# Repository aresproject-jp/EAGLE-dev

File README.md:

# EAGLE-dev
## projects
ARES3号機向けの回路の共同開発用ワークスペースです。
EAGLEのschファイルとbrdファイルを同じ名前のフォルダ内に保存して管理して下さい。
EAGLEの推奨バージョンは9.6.2です。
## libraries
各モジュールのライブラリを共有します。/computers /sensors /element /motor /connectorの5つの
フォルダを用意しています。以下の基準に従って分類して下さい。
- computers : コンピュータ及びマイクロコンピュータ　ex)jetson nano, raspberypi, arduino
- sensors   : 各センサモジュール　ex)BNO055, BMP180
- element   : 回路素子　ex)PchMosfet, DCDCconverter
- motor     : モーター関連のモジュール　ex)モータードライバ, エンコーダ
- connector : コネクタ類
## 3Dmodels
EAGLEにデフォルトで3Dデータが登録されていない部品の3Dデータ(*step)をアップロードしてください。
分類方法はlibrariesと同様です。
## documets
参考資料およびシステム図

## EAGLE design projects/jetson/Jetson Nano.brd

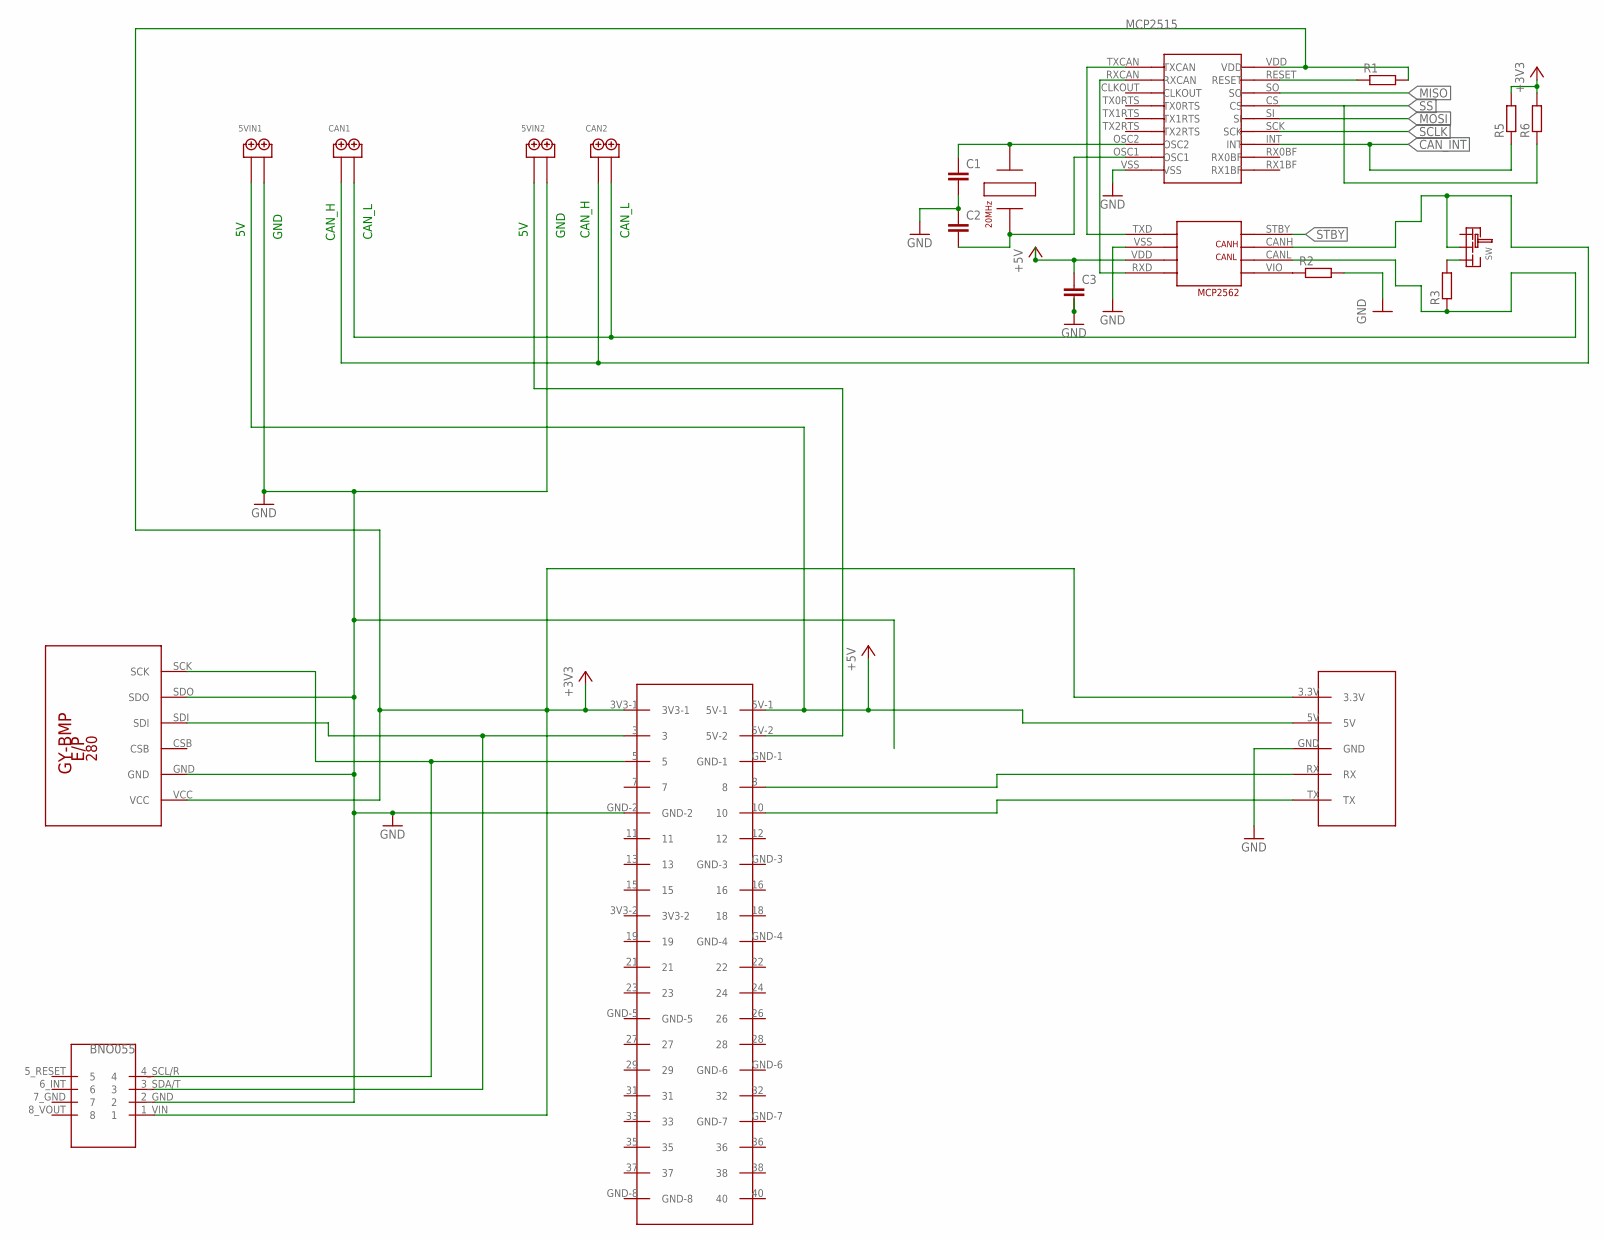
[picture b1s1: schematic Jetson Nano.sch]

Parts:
5VIN1, 5VIN2: 2PIN
C1, C2, C3: C-EU025-024X044; C025-024X044
CAN1, CAN2: 2PIN
JN1: JETSON_NANO
MCP1: MCP2515
R1, R2, R3, R5, R6: R-EU_0207/10; 0207/10
SW: SRIDE_SWITCH
U$1: GY-BPM280; GY-BMP280-FOOTPRINT
U$2: BNO055
U$3: WIRELESS_PINS
U$4: MCP2562
U$5: HUSG20

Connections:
5V_2: 5VIN2.P$1, JN1.5V-2
+3V3: JN1.3V3-1, MCP1.VDD, R1.2, R5.2, R6.2, U$1.VCC, U$2.1_VIN (1), U$3.3.3V
+5V_1: 5VIN1.P$1, C3.1, JN1.5V-1, U$3.5V, U$4.VDD
CAN_H2: CAN1.P$1, CAN2.P$1, SW.LR, U$4.CANH
CAN_INT: MCP1.INT, R5.1
GND: 5VIN1.P$2, 5VIN2.P$2, C1.2, C2.1, C3.2, JN1.GND-2, MCP1.VSS, U$1.GND, U$1.SDO, U$2.2_GND (2), U$3.GND, U$4.VSS
MISO: MCP1.SO
MOSI: MCP1.SI
unnamed: JN1.3, U$1.SDI, U$2.3_SDA/T (3)
unnamed: JN1.5, U$1.SCK, U$2.4_SCL/R (4)
unnamed: C1.1, MCP1.OSC2, U$5.A
unnamed: C2.2, MCP1.OSC1, U$5.B
unnamed: MCP1.TXCAN, U$4.TXD
unnamed: MCP1.RXCAN, U$4.RXD
unnamed: JN1.8, U$3.RX
unnamed: JN1.10, U$3.TX
unnamed: MCP1.RESET, R1.1
unnamed: R2.1, U$4.VIO
unnamed: R3.2, SW.R
unnamed: CAN1.P$2, CAN2.P$2, R3.1, U$4.CANL
SCLK: MCP1.SCK
SS: MCP1.CS, R6.1
STBY: U$4.STBY

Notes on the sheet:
GND
CAN_H
CAN_L

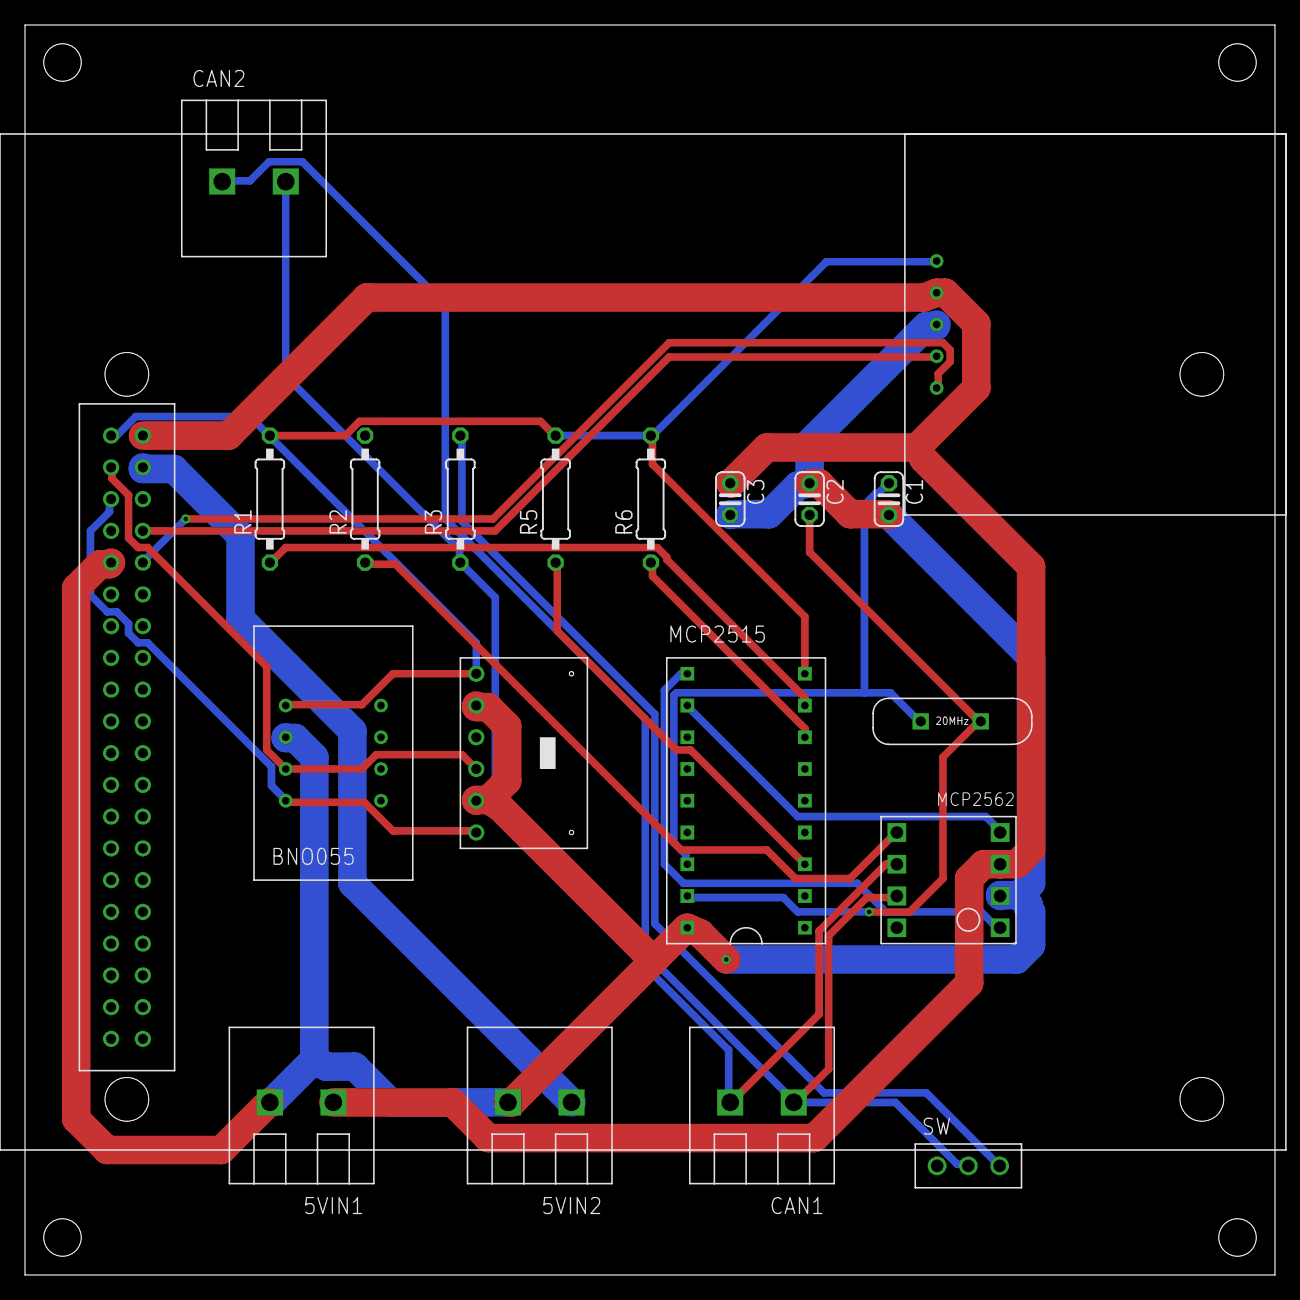
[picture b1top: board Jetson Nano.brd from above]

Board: 2 copper layers, 100.0 x 100.0 mm, 20 parts (0 on the bottom side), 19 nets.

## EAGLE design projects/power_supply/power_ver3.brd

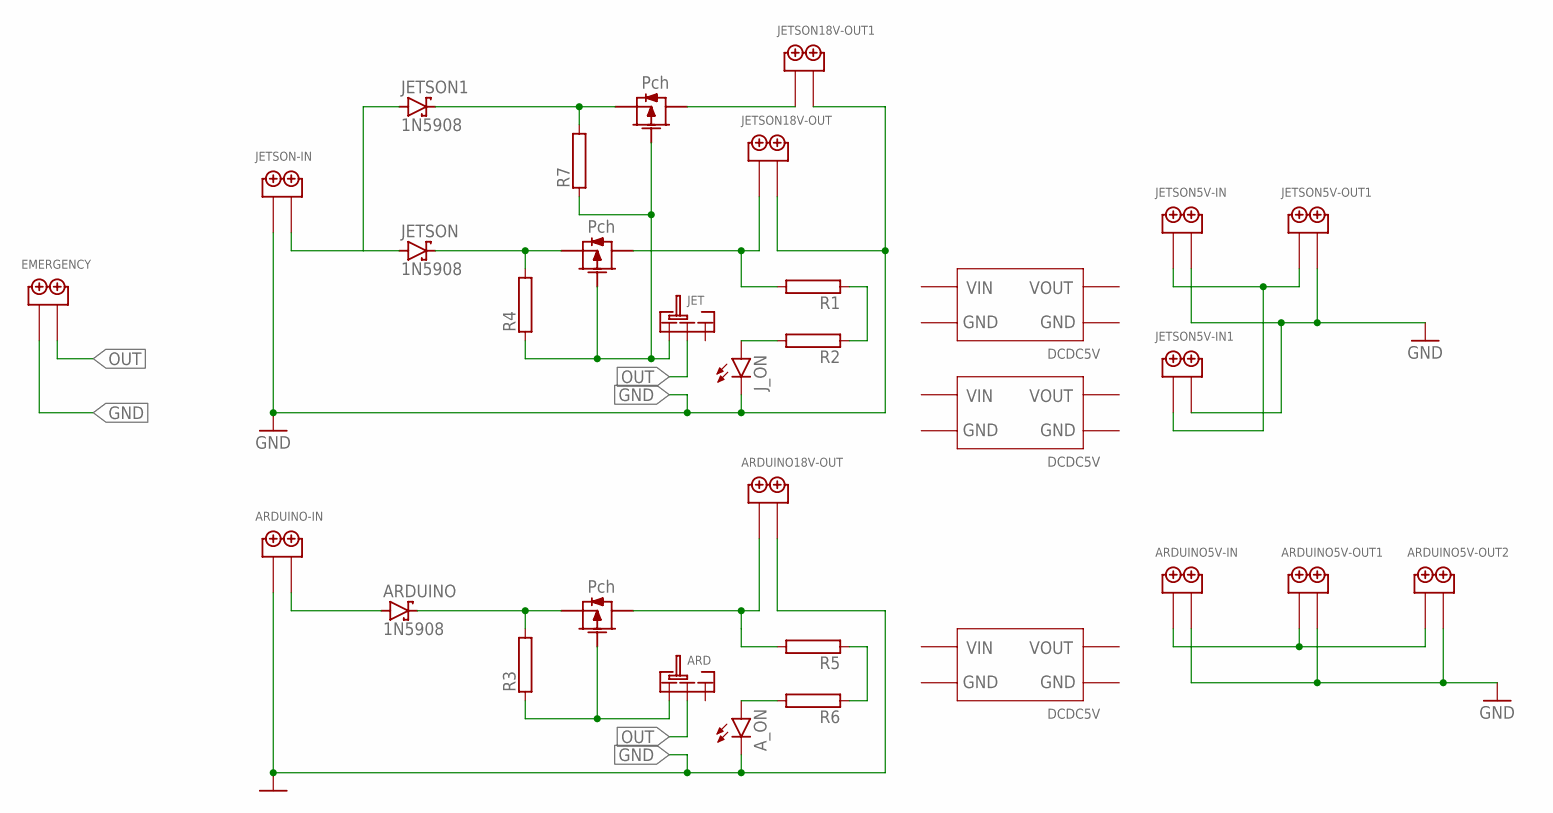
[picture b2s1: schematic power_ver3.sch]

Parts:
ARD: SRIDE_SWITCH
ARDUINO: 1N5908; C4111-15
ARDUINO5V-IN, ARDUINO5V-OUT1, ARDUINO5V-OUT2, ARDUINO18V-OUT: 2PIN
ARDUINO-IN: 2PIN
A_ON: LED5MM
EMERGENCY: 2PIN
JET: SRIDE_SWITCH
JETSON, JETSON1: 1N5908; C4111-15
JETSON5V-IN, JETSON5V-IN1, JETSON5V-OUT1, JETSON18V-OUT, JETSON18V-OUT1: 2PIN
JETSON-IN: 2PIN
J_ON: LED5MM
R1, R2, R3, R4, R5, R6, R7: RAC01; AC01
U$1, U$4, U$5: 2SJ334
U$2, U$6, U$23: DCDCDEV

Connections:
18V: JETSON.A, JETSON1.A, JETSON-IN.P$2
GND: ARDUINO5V-IN.P$2, ARDUINO5V-OUT1.P$2, ARDUINO5V-OUT2.P$2, ARDUINO18V-OUT.P$2, ARDUINO-IN.P$1, A_ON.K (C), EMERGENCY.P$1, JETSON5V-IN.P$2, JETSON5V-IN1.P$2, JETSON5V-OUT1.P$2, JETSON18V-OUT.P$2, JETSON18V-OUT1.P$2, JETSON-IN.P$1, J_ON.K (C)
MA: JETSON.C, R4.2, U$4.SOURCE
MA1: JETSON1.C, R7.2, U$1.SOURCE
MAC: JETSON18V-OUT.P$1, R1.2, U$4.DRAIN
MAD: JETSON5V-IN.P$1, JETSON5V-IN1.P$1, JETSON5V-OUT1.P$1
MBB: ARDUINO.A, ARDUINO-IN.P$2
MKK: ARDUINO.C, R3.2, U$5.SOURCE
ML: ARDUINO5V-IN.P$1, ARDUINO5V-OUT1.P$1, ARDUINO5V-OUT2.P$1
MOO: ARDUINO18V-OUT.P$1, R5.2, U$5.DRAIN
unnamed: ARD.L, R3.1, U$5.GATE
unnamed: J_ON.A, R2.2
unnamed: A_ON.A, R6.2
unnamed: JET.L, R4.1, R7.1, U$1.GATE, U$4.GATE
unnamed: JETSON18V-OUT1.P$1, U$1.DRAIN
unnamed: R5.1, R6.1
unnamed: R1.1, R2.1
OUT: ARD.LR, EMERGENCY.P$2, JET.LR

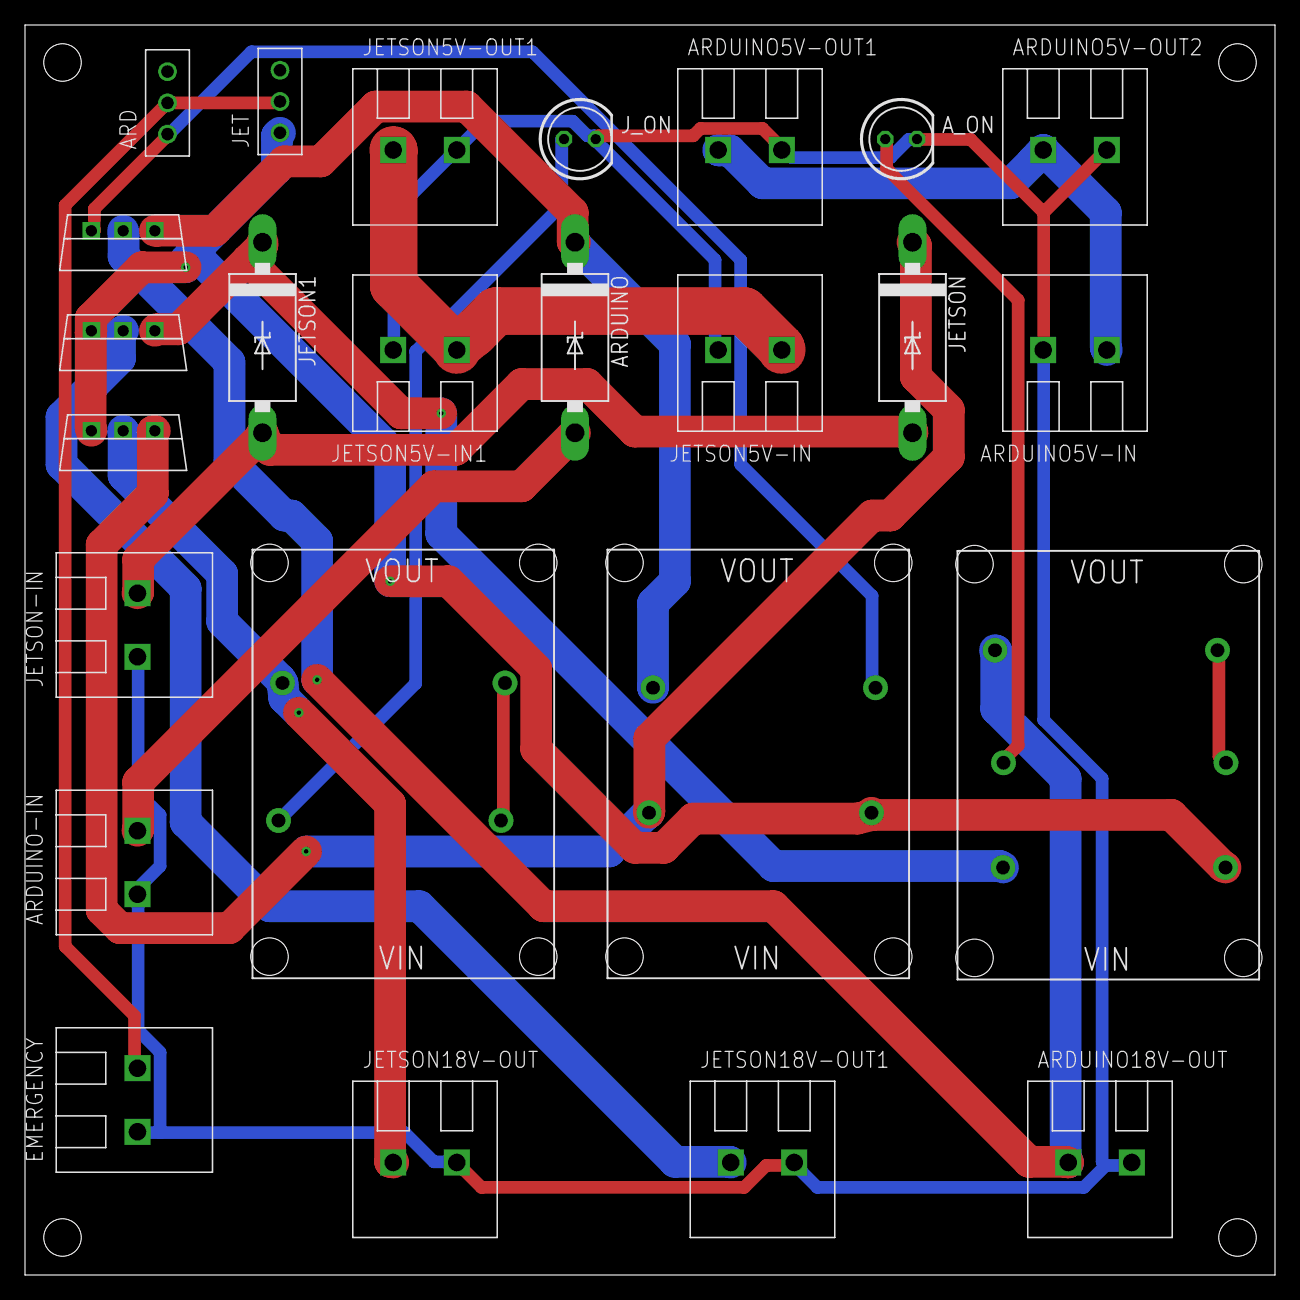
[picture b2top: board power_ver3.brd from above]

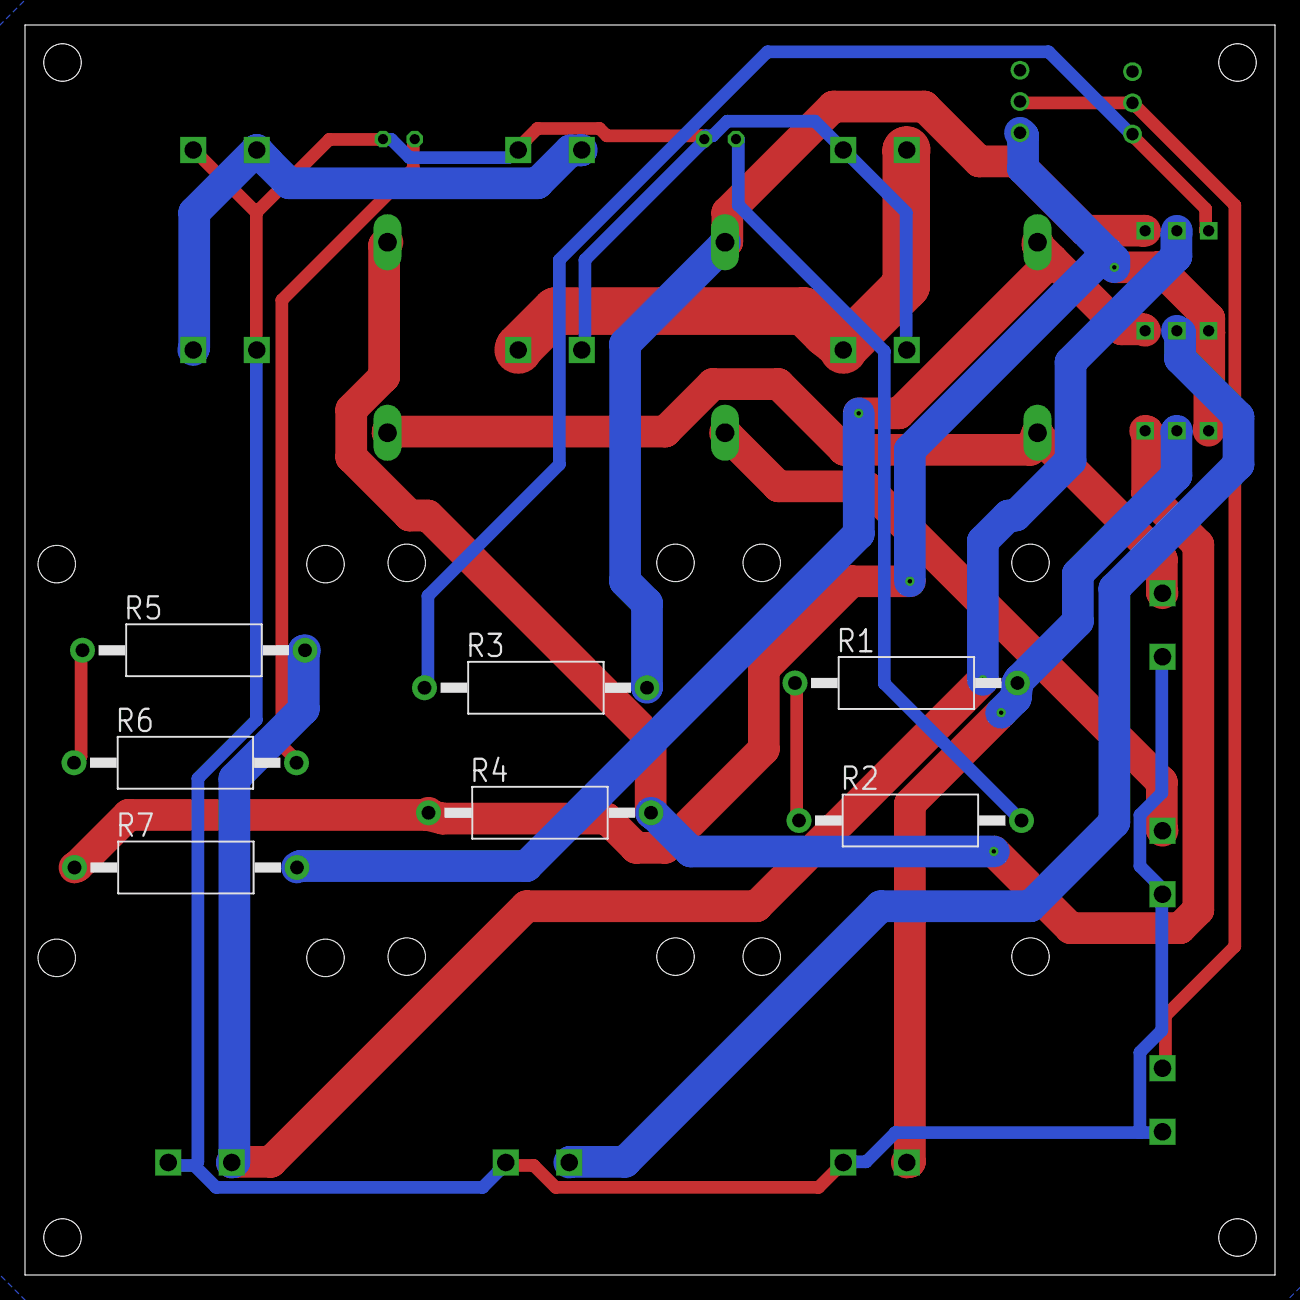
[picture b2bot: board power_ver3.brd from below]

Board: 2 copper layers, 100.0 x 100.0 mm, 32 parts (7 on the bottom side), 18 nets.

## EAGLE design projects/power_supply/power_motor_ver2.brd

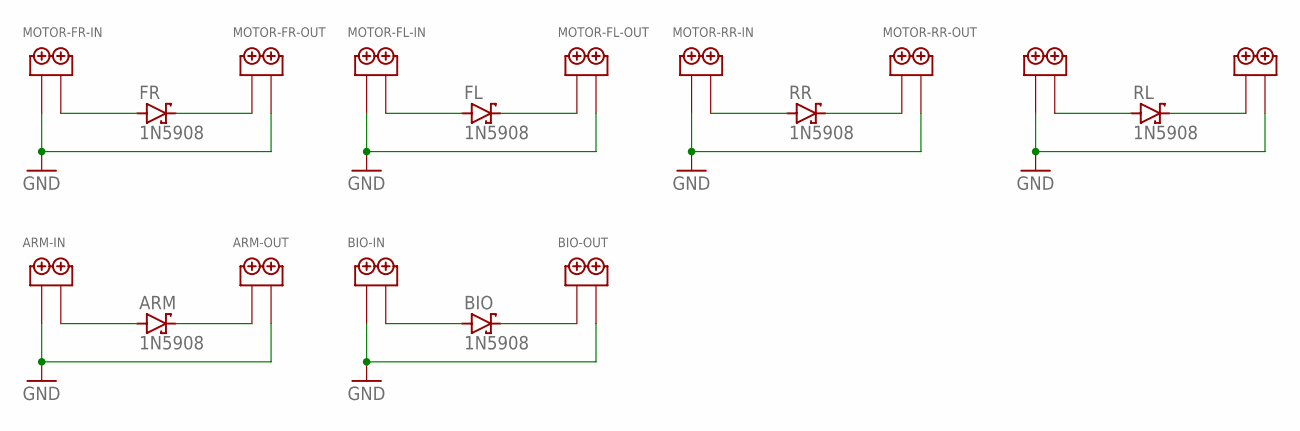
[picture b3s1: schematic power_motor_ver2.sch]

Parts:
ARM: 1N5908; C4111-15
ARM-IN: 2PIN
ARM-OUT: 2PIN
BIO: 1N5908; C4111-15
BIO-IN: 2PIN
BIO-OUT: 2PIN
FL: 1N5908; C4111-15
FR: 1N5908; C4111-15
MOTOR-FL-IN: 2PIN
MOTOR-FL-OUT: 2PIN
MOTOR-FR-IN: 2PIN
MOTOR-FR-OUT: 2PIN
MOTOR-RL-IN: 2PIN
MOTOR-RL-OUT: 2PIN
MOTOR-RR-IN: 2PIN
MOTOR-RR-OUT: 2PIN
RL: 1N5908; C4111-15
RR: 1N5908; C4111-15

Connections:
GND: ARM-IN.P$1, ARM-OUT.P$2, BIO-IN.P$1, BIO-OUT.P$2, MOTOR-FL-IN.P$1, MOTOR-FL-OUT.P$2, MOTOR-FR-IN.P$1, MOTOR-FR-OUT.P$2, MOTOR-RL-IN.P$1, MOTOR-RL-OUT.P$2, MOTOR-RR-IN.P$1, MOTOR-RR-OUT.P$2
unnamed: FR.A, MOTOR-FR-IN.P$2
unnamed: FR.C, MOTOR-FR-OUT.P$1
unnamed: FL.A, MOTOR-FL-IN.P$2
unnamed: FL.C, MOTOR-FL-OUT.P$1
unnamed: MOTOR-RR-IN.P$2, RR.A
unnamed: MOTOR-RR-OUT.P$1, RR.C
unnamed: MOTOR-RL-IN.P$2, RL.A
unnamed: MOTOR-RL-OUT.P$1, RL.C
unnamed: ARM.A, ARM-IN.P$2
unnamed: ARM.C, ARM-OUT.P$1
unnamed: BIO.A, BIO-IN.P$2
unnamed: BIO.C, BIO-OUT.P$1

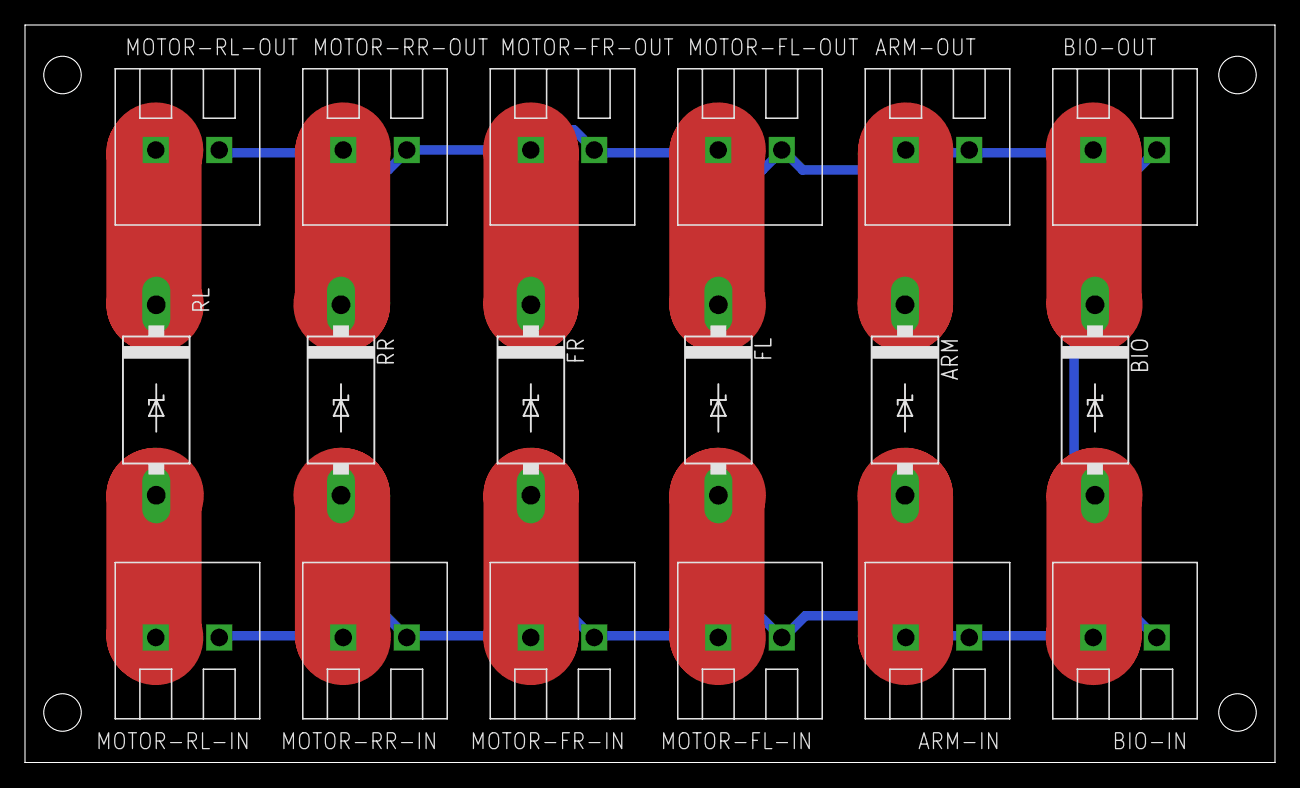
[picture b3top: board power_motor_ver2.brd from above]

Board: 2 copper layers, 100.0 x 59.0 mm, 18 parts (0 on the bottom side), 13 nets.

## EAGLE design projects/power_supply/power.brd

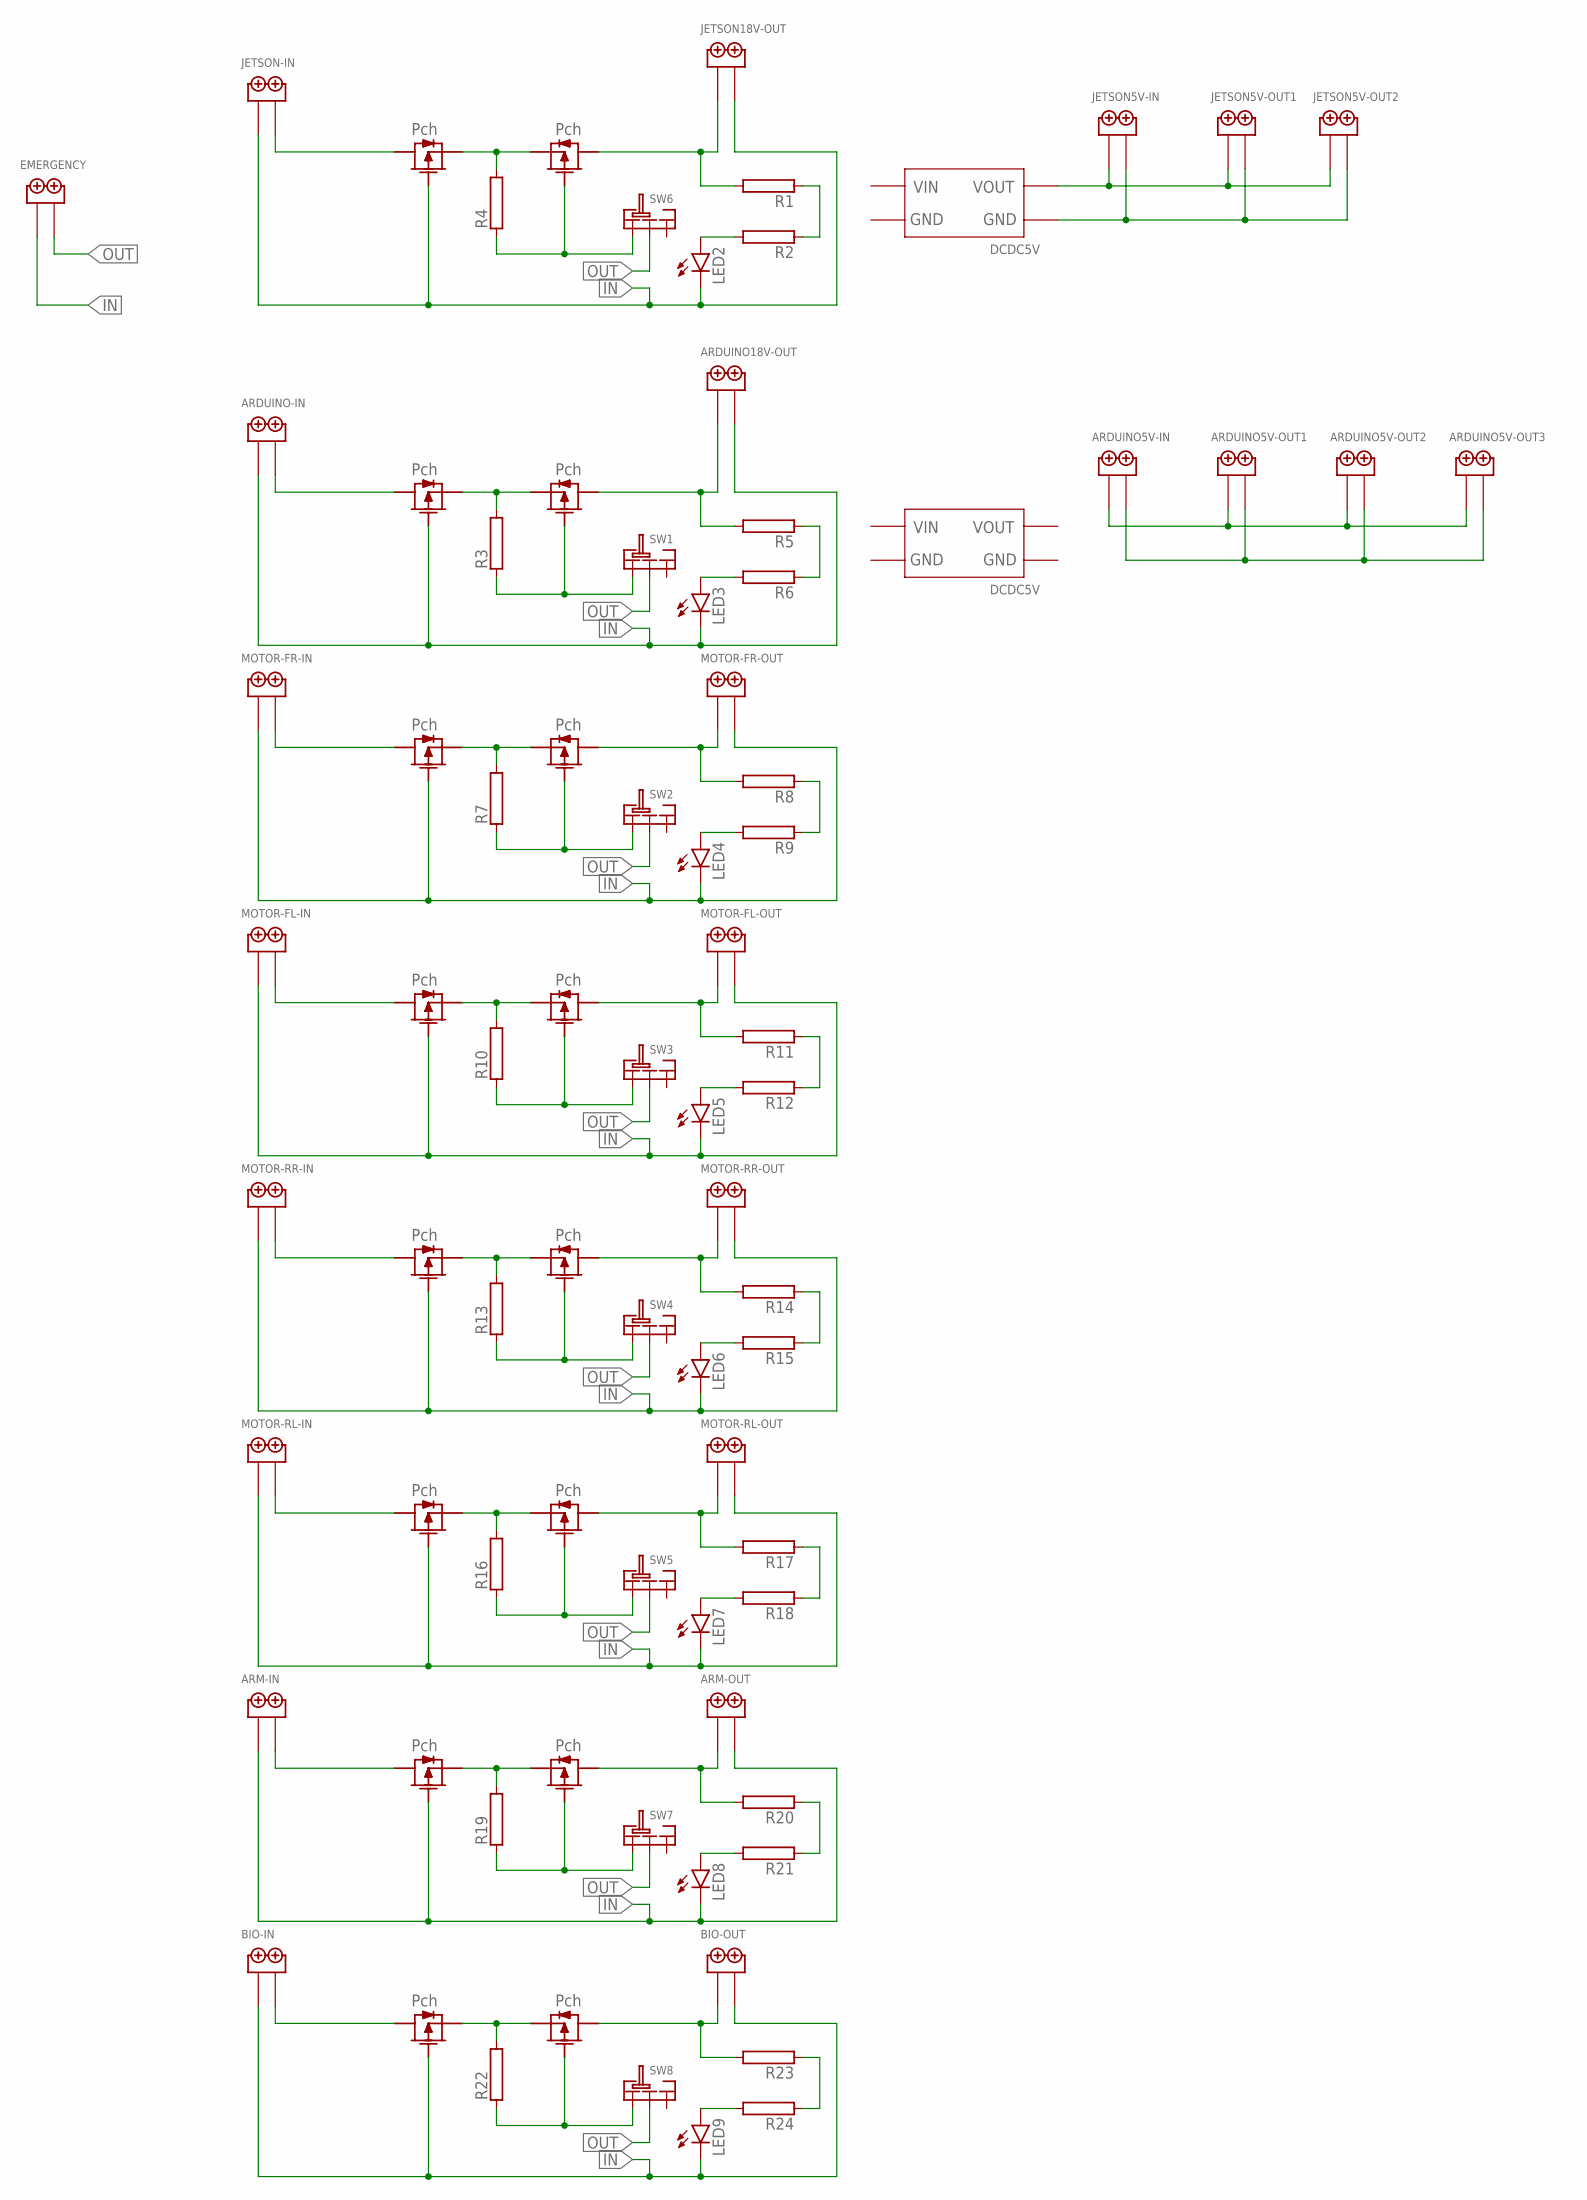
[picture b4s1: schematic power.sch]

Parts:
ARDUINO5V-IN, ARDUINO5V-OUT1, ARDUINO5V-OUT2, ARDUINO5V-OUT3, ARDUINO18V-OUT: 2PIN
ARDUINO-IN: 2PIN
ARM-IN: 2PIN
ARM-OUT: 2PIN
BIO-IN: 2PIN
BIO-OUT: 2PIN
EMERGENCY: 2PIN
JETSON5V-IN, JETSON5V-OUT1, JETSON5V-OUT2, JETSON18V-OUT: 2PIN
JETSON-IN: 2PIN
LED2, LED3, LED4, LED5, LED6, LED7, LED8, LED9: LED5MM
MOTOR-FL-IN: 2PIN
MOTOR-FL-OUT: 2PIN
MOTOR-FR-IN: 2PIN
MOTOR-FR-OUT: 2PIN
MOTOR-RL-IN: 2PIN
MOTOR-RL-OUT: 2PIN
MOTOR-RR-IN: 2PIN
MOTOR-RR-OUT: 2PIN
R1, R2, R3, R4, R5, R6, R7, R8, R9, R10, R11, R12, R13, R14, R15, R16, R17, R18, R19, R20, R21, R22, R23, R24: RAC01; AC01
SW1, SW2, SW3, SW4, SW5, SW6, SW7, SW8: SRIDE_SWITCH
U$1, U$3, U$4, U$5, U$7, U$8, U$10, U$11, U$13, U$14, U$16, U$17, U$20, U$21, U$24, U$25: 2SJ334
U$2, U$23: DCDCDEV

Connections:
18V: JETSON-IN.P$2, U$3.DRAIN
IN: ARDUINO18V-OUT.P$2, ARDUINO-IN.P$1, ARM-IN.P$1, ARM-OUT.P$2, BIO-IN.P$1, BIO-OUT.P$2, EMERGENCY.P$1, JETSON18V-OUT.P$2, JETSON-IN.P$1, LED2.K (C), LED3.K (C), LED4.K (C), LED5.K (C), LED6.K (C), LED7.K (C), LED8.K (C), LED9.K (C), MOTOR-FL-IN.P$1, MOTOR-FL-OUT.P$2, MOTOR-FR-IN.P$1, MOTOR-FR-OUT.P$2, MOTOR-RL-IN.P$1, MOTOR-RL-OUT.P$2, MOTOR-RR-IN.P$1, MOTOR-RR-OUT.P$2, U$1.GATE, U$3.GATE, U$7.GATE, U$10.GATE, U$13.GATE, U$16.GATE, U$20.GATE, U$24.GATE
MA: R4.2, U$3.SOURCE, U$4.SOURCE
MAC: JETSON18V-OUT.P$1, R1.2, U$4.DRAIN
MAD: JETSON5V-IN.P$1, JETSON5V-OUT1.P$1, JETSON5V-OUT2.P$1; also elsewhere on the board
MBB: ARDUINO-IN.P$2, U$1.DRAIN
MBV: R13.2, U$13.SOURCE, U$14.SOURCE
MCX: R16.2, U$16.SOURCE, U$17.SOURCE
MDSDS: BIO-IN.P$2, U$24.DRAIN
MGG: ARM-IN.P$2, U$20.DRAIN
MH: R10.2, U$10.SOURCE, U$11.SOURCE
MHGF: ARM-OUT.P$1, R20.2, U$21.DRAIN
MHH: MOTOR-RR-OUT.P$1, R14.2, U$14.DRAIN
MHHHH: BIO-OUT.P$1, R23.2, U$25.DRAIN
MJUY: R22.2, U$24.SOURCE, U$25.SOURCE
MKK: R3.2, U$1.SOURCE, U$5.SOURCE
ML: ARDUINO5V-IN.P$1, ARDUINO5V-OUT1.P$1, ARDUINO5V-OUT2.P$1, ARDUINO5V-OUT3.P$1
MN: MOTOR-RL-IN.P$2, U$16.DRAIN
MOO: ARDUINO18V-OUT.P$1, R5.2, U$5.DRAIN
MS: R7.2, U$7.SOURCE, U$8.SOURCE
MU: MOTOR-FR-IN.P$2, U$7.DRAIN
MV: MOTOR-FL-OUT.P$1, R11.2, U$11.DRAIN
MVVV: R19.2, U$20.SOURCE, U$21.SOURCE
MX: MOTOR-RR-IN.P$2, U$13.DRAIN
MY: MOTOR-FL-IN.P$2, U$10.DRAIN
MZZ: MOTOR-RL-OUT.P$1, R17.2, U$17.DRAIN
unnamed: R3.1, SW1.L, U$5.GATE
unnamed: LED2.A, R2.2
unnamed: LED3.A, R6.2
unnamed: LED4.A, R9.2
unnamed: R5.1, R6.1
unnamed: LED5.A, R12.2
unnamed: R22.1, SW8.L, U$25.GATE
unnamed: ARDUINO5V-IN.P$2, ARDUINO5V-OUT1.P$2, ARDUINO5V-OUT2.P$2, ARDUINO5V-OUT3.P$2
unnamed: R7.1, SW2.L, U$8.GATE
unnamed: LED6.A, R15.2
unnamed: LED7.A, R18.2
unnamed: MOTOR-FR-OUT.P$1, R8.2, U$8.DRAIN
unnamed: R8.1, R9.1
unnamed: LED8.A, R21.2
unnamed: LED9.A, R24.2
unnamed 41: JETSON5V-IN.P$2, JETSON5V-OUT1.P$2, JETSON5V-OUT2.P$2; also elsewhere on the board
unnamed: R10.1, SW3.L, U$11.GATE
unnamed: R11.1, R12.1
unnamed: R13.1, SW4.L, U$14.GATE
unnamed: R14.1, R15.1
unnamed: R16.1, SW5.L, U$17.GATE
unnamed: R17.1, R18.1
unnamed: R4.1, SW6.L, U$4.GATE
unnamed: R1.1, R2.1
unnamed: R19.1, SW7.L, U$21.GATE
unnamed: R23.1, R24.1
unnamed: R20.1, R21.1
OUT: EMERGENCY.P$2, SW1.LR, SW2.LR, SW3.LR, SW4.LR, SW5.LR, SW6.LR, SW7.LR, SW8.LR

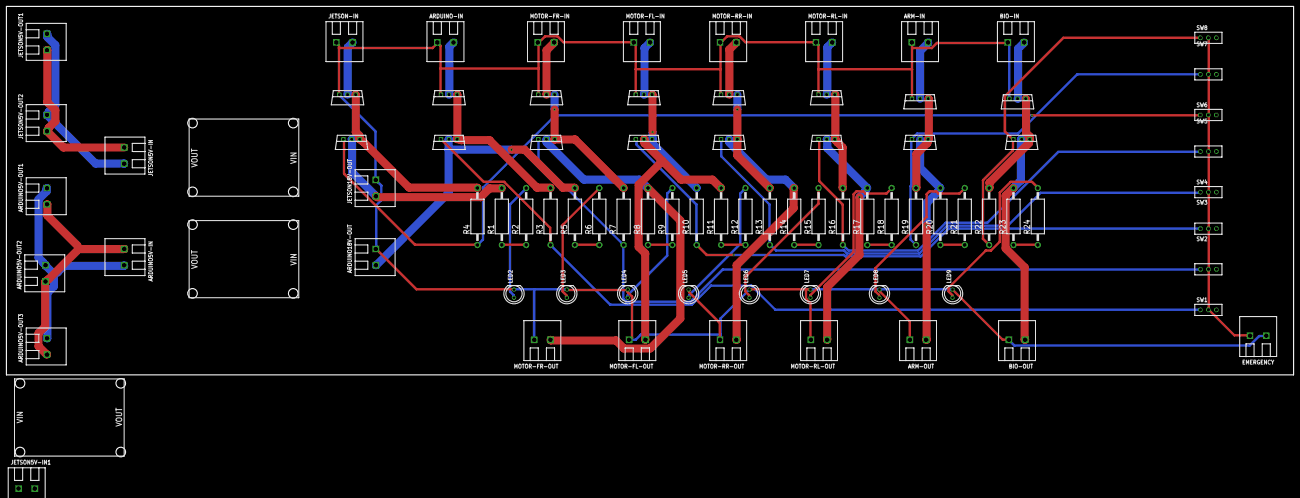
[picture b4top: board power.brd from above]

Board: 2 copper layers, 402.6 x 115.2 mm, 84 parts (0 on the bottom side), 54 nets.

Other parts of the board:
JETSON5V-IN1: 2PIN
U$6: DCDCDEV

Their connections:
MAD: JETSON5V-IN1.P$2; also elsewhere on the board
unnamed 41: JETSON5V-IN1.P$1; also elsewhere on the board

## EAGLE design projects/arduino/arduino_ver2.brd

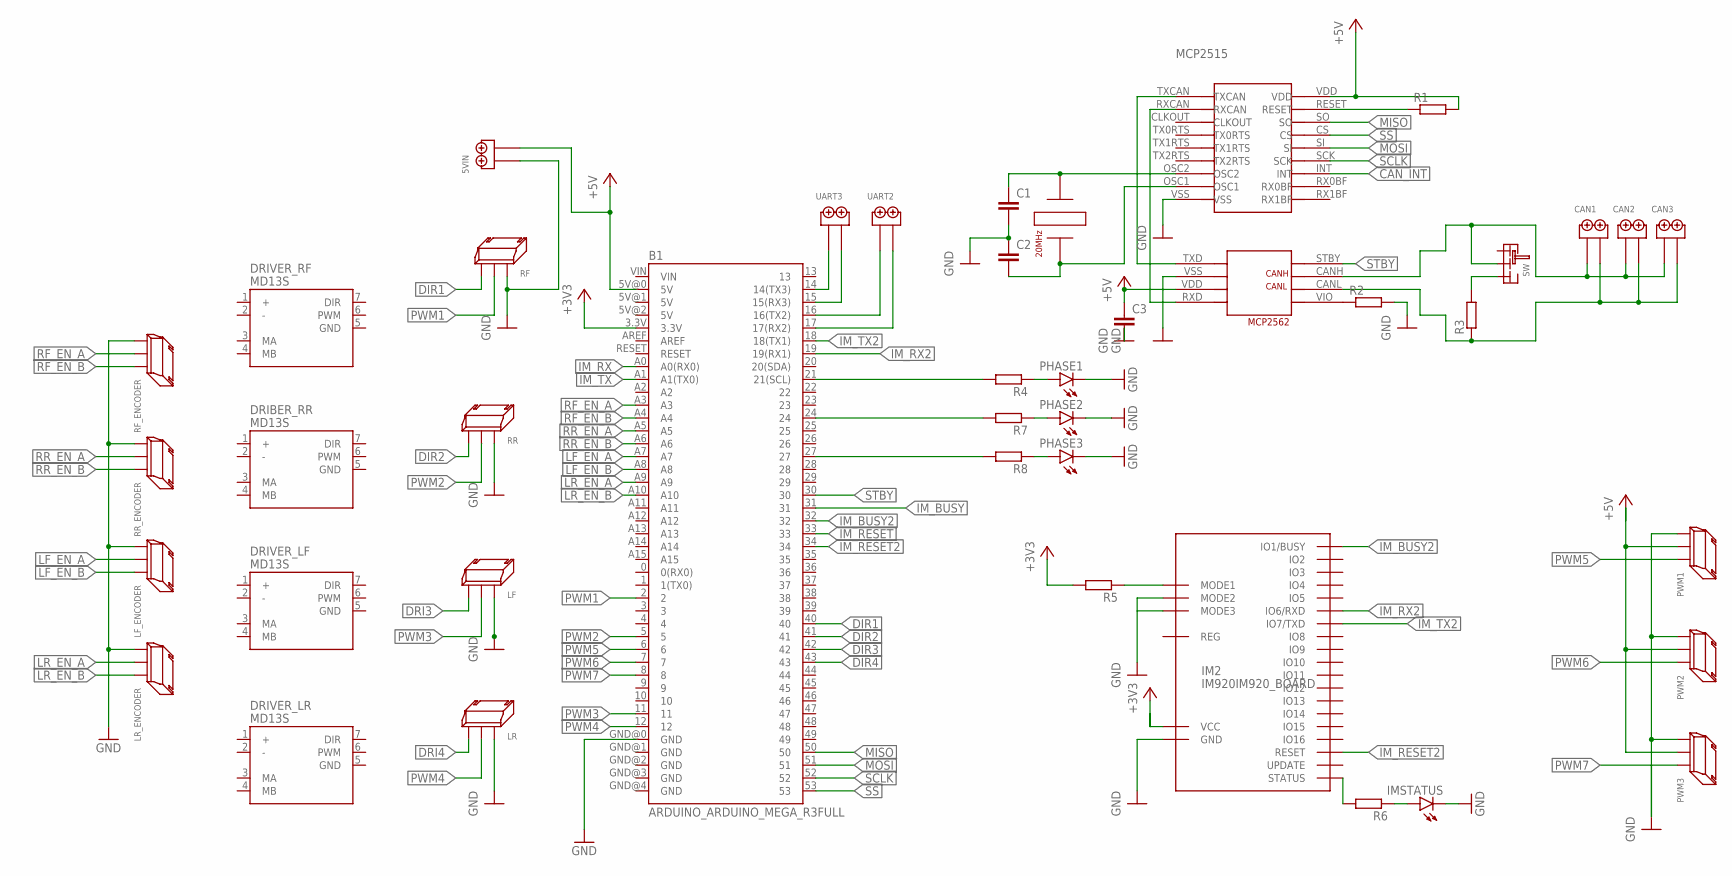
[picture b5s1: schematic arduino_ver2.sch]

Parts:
5VIN: 2PIN
B1: ARDUINO_ARDUINO_MEGA_R3FULL; ARDUINO_ARDUINO_MEGA
C1, C2, C3: C-EU025-024X044; C025-024X044
CAN1, CAN2, CAN3: 2PIN
DRIBER_RR: MD13S
DRIVER_LF: MD13S
DRIVER_LR: MD13S
DRIVER_RF: MD13S
IM2: IM920IM920_BOARD; IM920_BOARD
IMSTATUS: LED3MM
LF: 3PIN_SIDE
LF_ENCODER: 3PIN_SIDE
LR: 3PIN_SIDE
LR_ENCODER: 3PIN_SIDE
MCP2: MCP2515
PHASE1, PHASE2, PHASE3: LED3MM
PWM1, PWM2, PWM3: 3PIN_SIDE
R1, R2, R3, R4, R5, R6, R7, R8: R-EU_0207/10; 0207/10
RF: 3PIN_SIDE
RF_ENCODER: 3PIN_SIDE
RR: 3PIN_SIDE
RR_ENCODER: 3PIN_SIDE
SW: SRIDE_SWITCH
U$1: MCP2562
U$3: HUSG20
UART2, UART3: 2PIN

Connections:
+3V3: B1.3.3V, R5.2
+5V: 5VIN.P$2, B1.5V@0 (5V), C3.1, MCP2.VDD, R1.2, U$1.VDD
CAN_INT: MCP2.INT
DIR1: B1.40, RF.P$2
DIR2: B1.41, RR.P$2
DIR3: B1.42
DIR4: B1.43
DRI3: LF.P$2
DRI4: LR.P$2
GND: B1.GND@0 (GND), IMSTATUS.K (C), LF_ENCODER.P$2, LR_ENCODER.P$2, PHASE1.K (C), PHASE2.K (C), PHASE3.K (C), R2.2, RF_ENCODER.P$2, RR_ENCODER.P$2
IM_BUSY: B1.31
IM_BUSY2: B1.32, IM2.IO1 (IO1/BUSY)
IM_RESET: B1.33
IM_RESET2: B1.34, IM2.IO25 (RESET)
IM_RX: B1.A0 (A0(RX0))
IM_RX2: B1.19 (19(RX1)), IM2.IO6 (IO6/RXD)
IM_TX: B1.A1 (A1(TX0))
IM_TX2: B1.18 (18(TX1)), IM2.IO7 (IO7/TXD)
LF_EN_A: B1.A7, LF_ENCODER.P$1
LF_EN_B: B1.A8, LF_ENCODER.P$3
LR_EN_A: B1.A9, LR_ENCODER.P$1
LR_EN_B: B1.A10, LR_ENCODER.P$3
MISO: B1.50, MCP2.SO
MOSI: B1.51, MCP2.SI
unnamed: C1.1, MCP2.OSC2, U$3.A
unnamed: C2.2, MCP2.OSC1, U$3.B
unnamed: MCP2.TXCAN, U$1.TXD
unnamed: MCP2.RXCAN, U$1.RXD
unnamed: MCP2.RESET, R1.1
unnamed: R2.1, U$1.VIO
unnamed: CAN1.P$1, CAN2.P$1, CAN3.P$1, SW.LR, U$1.CANH
unnamed: R3.2, SW.R
unnamed: B1.21 (21(SCL)), R4.2
unnamed: CAN1.P$2, CAN2.P$2, CAN3.P$2, R3.1, U$1.CANL
unnamed: PHASE1.A, R4.1
unnamed: PWM1.P$2, PWM2.P$2, PWM3.P$2
unnamed: IM2.IO21 (STATUS), R6.2
unnamed: IMSTATUS.A, R6.1
unnamed: PWM1.P$1, PWM2.P$1, PWM3.P$1
unnamed: B1.24, R7.2
unnamed: PHASE2.A, R7.1
unnamed: B1.27, R8.2
unnamed: PHASE3.A, R8.1
unnamed: B1.14 (14(TX3)), UART3.P$1
unnamed: B1.15 (15(RX3)), UART3.P$2
unnamed: B1.16 (16(TX2)), UART2.P$1
unnamed: B1.17 (17(RX2)), UART2.P$2
unnamed: IM2.IO17 (MODE1), R5.1
PWM1: B1.2, RF.P$1
PWM2: B1.5, RR.P$1
PWM3: B1.11, LF.P$1
PWM4: B1.12, LR.P$1
PWM5: B1.6, PWM1.P$3
PWM6: B1.7, PWM2.P$3
PWM7: B1.8, PWM3.P$3
RF_EN_A: B1.A3, RF_ENCODER.P$1
RF_EN_B: B1.A4, RF_ENCODER.P$3
RR_EN_A: B1.A5, RR_ENCODER.P$1
RR_EN_B: B1.A6, RR_ENCODER.P$3
SCLK: B1.52, MCP2.SCK
SS: B1.53, MCP2.CS
STBY: B1.30, U$1.STBY
V-: 5VIN.P$1, C1.2, C2.1, C3.2, IM2.IO18 (MODE2), IM2.IO24 (GND), LF.P$3, LR.P$3, MCP2.VSS, RF.P$3, RR.P$3, U$1.VSS
